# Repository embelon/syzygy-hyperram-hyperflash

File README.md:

# syzygy-hyperram-hyperflash
Syzygy Pod PCB with HyperRAM and HyperFlash memories

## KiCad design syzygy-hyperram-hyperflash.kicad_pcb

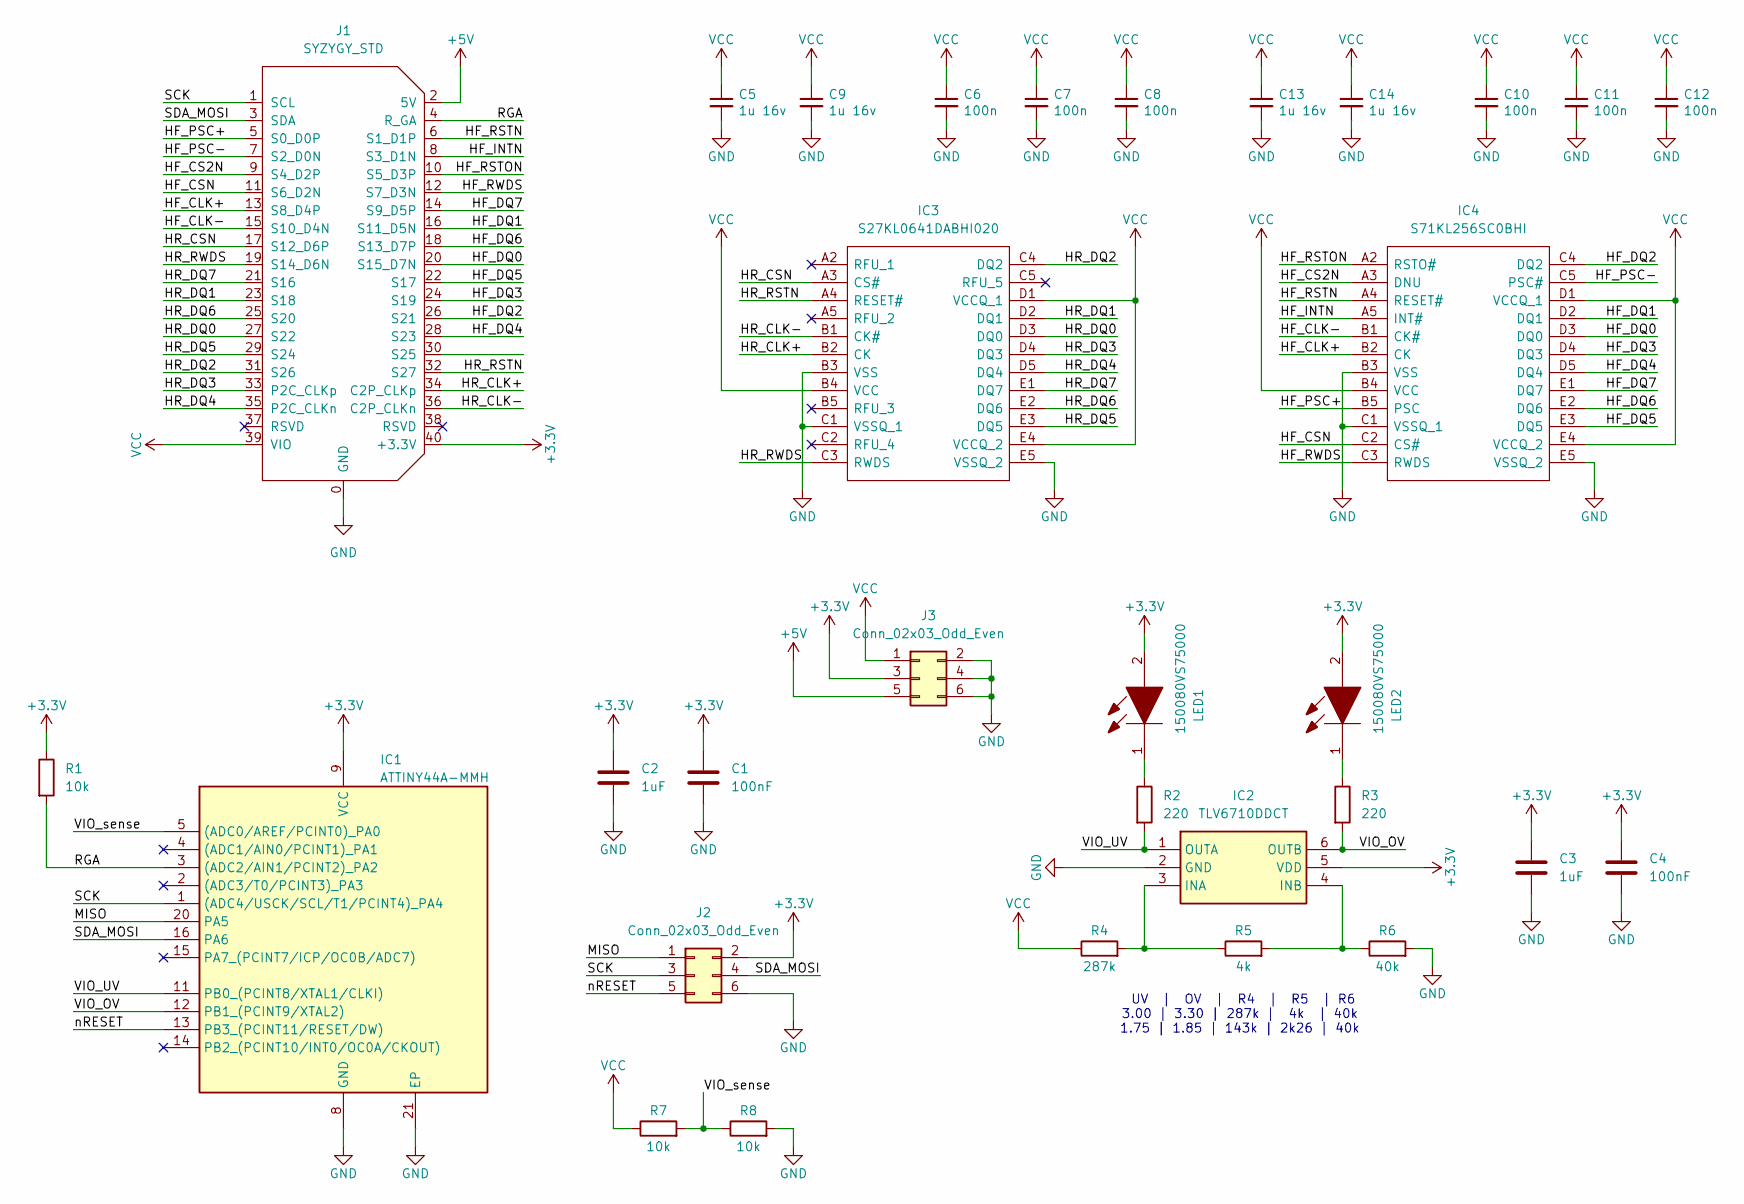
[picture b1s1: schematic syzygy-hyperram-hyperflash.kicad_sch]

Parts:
C1, C4: 100nF; C_0603_1608Metric_Pad1.08x0.95mm_HandSolder
C2, C3: 1uF; C_0805_2012Metric_Pad1.18x1.45mm_HandSolder
C5, C9, C13, C14: 1u 16v; C_0805_2012Metric_Pad1.18x1.45mm_HandSolder; Part CL10A105KO8NNNC
C6, C7, C8, C10, C11, C12: 100n; C_0603_1608Metric_Pad1.08x0.95mm_HandSolder; Part CGA3E2X7R1H223K080AA
IC1: ATTINY44A-MMH; QFN45P300X300X85-21N; Mouser Part Number 556-ATTINY44A-MMH
IC2: TLV6710DDCT; SOT95P280X100-6N; Mouser Part Number 595-TLV6710DDCT
IC3: S27KL0641DABHI020; BGA24C100P5X5_600X800X100; Manufacturer_Part_Number S27KL0641DABHI020; Mouser Part Number 727-S27KL0641DABHI02
IC4: S71KL256SC0BHI; BGA24C100P5X5_600X800X100; Mouser Part Number 727-S26KL128SDABHI02
J1: SYZYGY_STD; QTE-020-XX-YYY-D-A; Manufacturer_PN QTE-020-01-F-D-A
J2, J3: Conn_02x03_Odd_Even; PinHeader_2x03_P2.54mm_Vertical
LED1: 150080VS75000; LEDC2012X80N; Mouser Part Number 710-150080VS75000
LED2: 150080VS75000; LEDC2012X80N; Mouser Part Number 710-150080BS75000
R1, R7, R8: 10k; R_0603_1608Metric_Pad0.98x0.95mm_HandSolder
R2, R3: 220; R_0603_1608Metric_Pad0.98x0.95mm_HandSolder
R4: 287k; R_0603_1608Metric_Pad0.98x0.95mm_HandSolder
R5: 4k; R_0603_1608Metric_Pad0.98x0.95mm_HandSolder
R6: 40k; R_0603_1608Metric_Pad0.98x0.95mm_HandSolder

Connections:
+3.3V: C1.1, C2.1, C3.1, C4.1, IC1.9 (VCC), IC2.5 (VDD), J1.40 (+3.3V), J2.2, J3.3, LED1.2, LED2.2, R1.1
+5V: J1.2 (5V), J3.5
/HF_CLK+: IC4.B2 (CK), J1.13 (S8_D4P)
/HF_CLK-: IC4.B1 (CK#), J1.15 (S10_D4N)
/HF_CS2N: IC4.A3 (DNU), J1.9 (S4_D2P)
/HF_CSN: IC4.C2 (CS#), J1.11 (S6_D2N)
/HF_DQ0: IC4.D3 (DQ0), J1.20 (S15_D7N)
/HF_DQ1: IC4.D2 (DQ1), J1.16 (S11_D5N)
/HF_DQ2: IC4.C4 (DQ2), J1.26 (S21)
/HF_DQ3: IC4.D4 (DQ3), J1.24 (S19)
/HF_DQ4: IC4.D5 (DQ4), J1.28 (S23)
/HF_DQ5: IC4.E3 (DQ5), J1.22 (S17)
/HF_DQ6: IC4.E2 (DQ6), J1.18 (S13_D7P)
/HF_DQ7: IC4.E1 (DQ7), J1.14 (S9_D5P)
/HF_INTN: IC4.A5 (INT#), J1.8 (S3_D1N)
/HF_PSC+: IC4.B5 (PSC), J1.5 (S0_D0P)
/HF_PSC-: IC4.C5 (PSC#), J1.7 (S2_D0N)
/HF_RSTN: IC4.A4 (RESET#), J1.6 (S1_D1P)
/HF_RSTON: IC4.A2 (RSTO#), J1.10 (S5_D3P)
/HF_RWDS: IC4.C3 (RWDS), J1.12 (S7_D3N)
/HR_CLK+: IC3.B2 (CK), J1.34 (C2P_CLKp)
/HR_CLK-: IC3.B1 (CK#), J1.36 (C2P_CLKn)
/HR_CSN: IC3.A3 (CS#), J1.17 (S12_D6P)
/HR_DQ0: IC3.D3 (DQ0), J1.27 (S22)
/HR_DQ1: IC3.D2 (DQ1), J1.23 (S18)
/HR_DQ2: IC3.C4 (DQ2), J1.31 (S26)
/HR_DQ3: IC3.D4 (DQ3), J1.33 (P2C_CLKp)
/HR_DQ4: IC3.D5 (DQ4), J1.35 (P2C_CLKn)
/HR_DQ5: IC3.E3 (DQ5), J1.29 (S24)
/HR_DQ6: IC3.E2 (DQ6), J1.25 (S20)
/HR_DQ7: IC3.E1 (DQ7), J1.21 (S16)
/HR_RSTN: IC3.A4 (RESET#), J1.32 (S27)
/HR_RWDS: IC3.C3 (RWDS), J1.19 (S14_D6N)
/MISO: IC1.20 (PA5), J2.1
/RGA: IC1.3 ((ADC2/AIN1/PCINT2)_PA2), J1.4 (R_GA), R1.2
/SCK: IC1.1 ((ADC4/USCK/SCL/T1/PCINT4)_PA4), J1.1 (SCL), J2.3
/SDA_MOSI: IC1.16 (PA6), J1.3 (SDA), J2.4
/VIO_OV: IC1.12 (PB1_(PCINT9/XTAL2)), IC2.6 (OUTB), R3.2
/VIO_UV: IC1.11 (PB0_(PCINT8/XTAL1/CLKI)), IC2.1 (OUTA), R2.2
/VIO_sense: IC1.5 ((ADC0/AREF/PCINT0)_PA0), R7.2, R8.1
/nRESET: IC1.13 (PB3_(PCINT11/RESET/DW)), J2.5
GND: C1.2, C2.2, C3.2, C4.2, C5.2, C6.2, C7.2, C8.2, C9.2, C10.2, C11.2, C12.2, C13.2, C14.2, IC1.8 (GND), IC1.21 (EP), IC2.2 (GND), IC3.B3 (VSS), IC3.C1 (VSSQ_1), IC3.E5 (VSSQ_2), IC4.B3 (VSS), IC4.C1 (VSSQ_1), IC4.E5 (VSSQ_2), J1.0 (GND), J2.6, J3.2, J3.4, J3.6, R6.2, R8.2
unnamed: IC2.3 (INA), R4.2, R5.1
unnamed: IC2.4 (INB), R5.2, R6.1
unnamed: LED1.1, R2.1
unnamed: LED2.1, R3.1
VCC: C5.1, C6.1, C7.1, C8.1, C9.1, C10.1, C11.1, C12.1, C13.1, C14.1, IC3.B4 (VCC), IC3.D1 (VCCQ_1), IC3.E4 (VCCQ_2), IC4.B4 (VCC), IC4.D1 (VCCQ_1), IC4.E4 (VCCQ_2), J1.39 (VIO), J3.1, R4.1, R7.1

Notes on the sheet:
UV | OV | R4 | R5 | R6 3.00 | 3.30 | 287k | 4k | 40k 1.75 | 1.85 | 143k | 2k26 | 40k

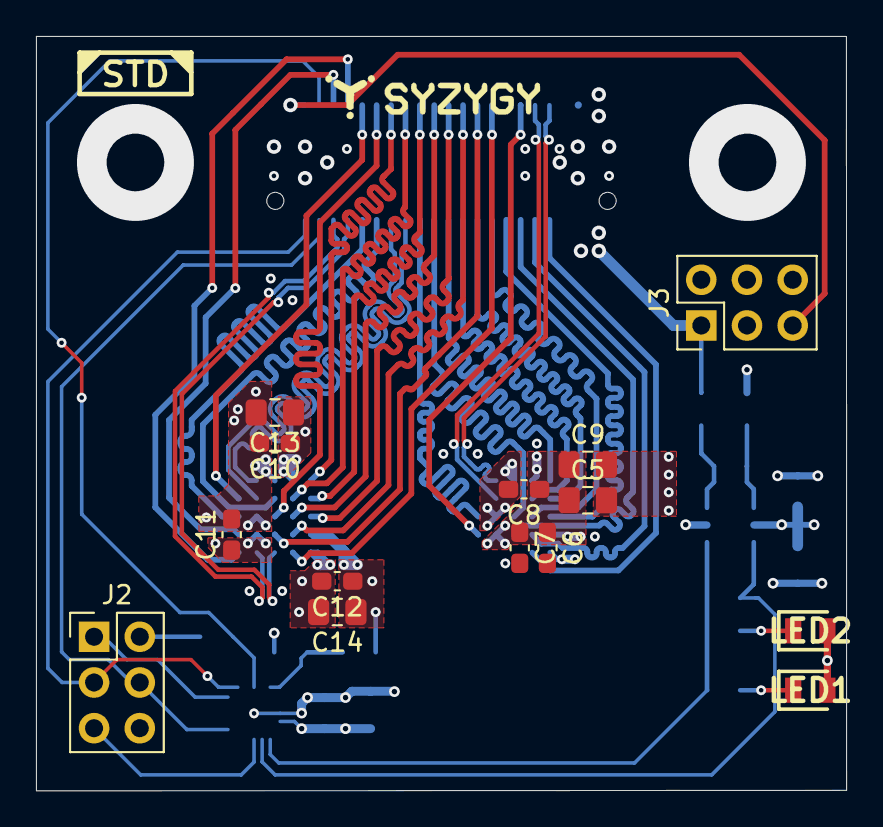
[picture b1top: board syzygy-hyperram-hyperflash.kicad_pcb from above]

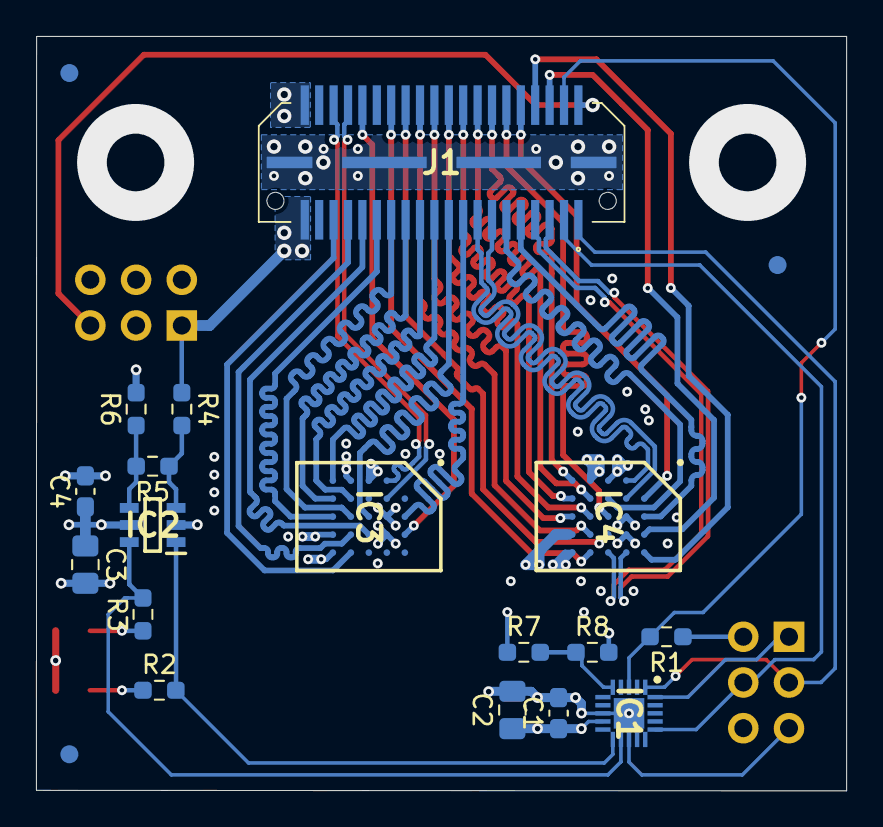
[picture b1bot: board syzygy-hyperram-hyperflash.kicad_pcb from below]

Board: 4 copper layers, 45.0 x 41.9 mm, 34 parts (20 on the bottom side), 47 nets.

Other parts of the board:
FID5, FID6, FID8: Fiducial; Fiducial_1mm_Mask2mm

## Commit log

2024-06-25 Created empty project and added symbol and footprint libraries
2024-06-25 Added TLV6710 and ATTINY44A to symbol library.
2024-06-25 Added footprints for ATTINY44A and TLV6710 to project library
2024-06-25 Modified ATTINY44A symbol
2024-06-25 Added *.bak files to ignore list
2024-06-25 Defined stackup and constraints and diff pairs parameters for 100 Ohm impedance
2024-06-26 Removed forgotten DNC pin on ATTINY44A
2024-06-26 Connected all desired components on schematic
2024-06-26 Added PCB template for STD-SYZYGY
2024-06-26 Adjusted QTE footprint for easier manual soldering
2024-06-26 Rearranged HyperRAM signals to prioritize data and rwds. Added header with supply voltages.
2024-06-26 Updated PCB after latest changes in schematic
2024-06-26 Fixed patterns for differential pairs net classes
2024-06-27 Rearranging HyperRAM (IC3) signals to simplify routing
2024-06-27 Fixed via drill and clearance settings
2024-06-27 Routed all signals to HyperRAM (IC3)
2024-06-27 Added more filtering capacitors for HyperRAM and HyperFLash supply
2024-06-28 Optimizing signal assignements to simplify routing HyperFlash
2024-06-28 First, still not complete, try to route HyperFlash
2024-07-07 Rearranged few signals to finish routing HyperFlash
2024-07-07 Finished routing HyperFlash with equalized trace length
2025-08-16 Removed unnecessary holes to make pcb smaller. Rearranged signals connected to ATTiny.
2025-08-16 Make PCB smaller, by reaaranging signals and footprints. First try of routing ATTiny.
2025-08-16 Route all non-power / non-plane signals
